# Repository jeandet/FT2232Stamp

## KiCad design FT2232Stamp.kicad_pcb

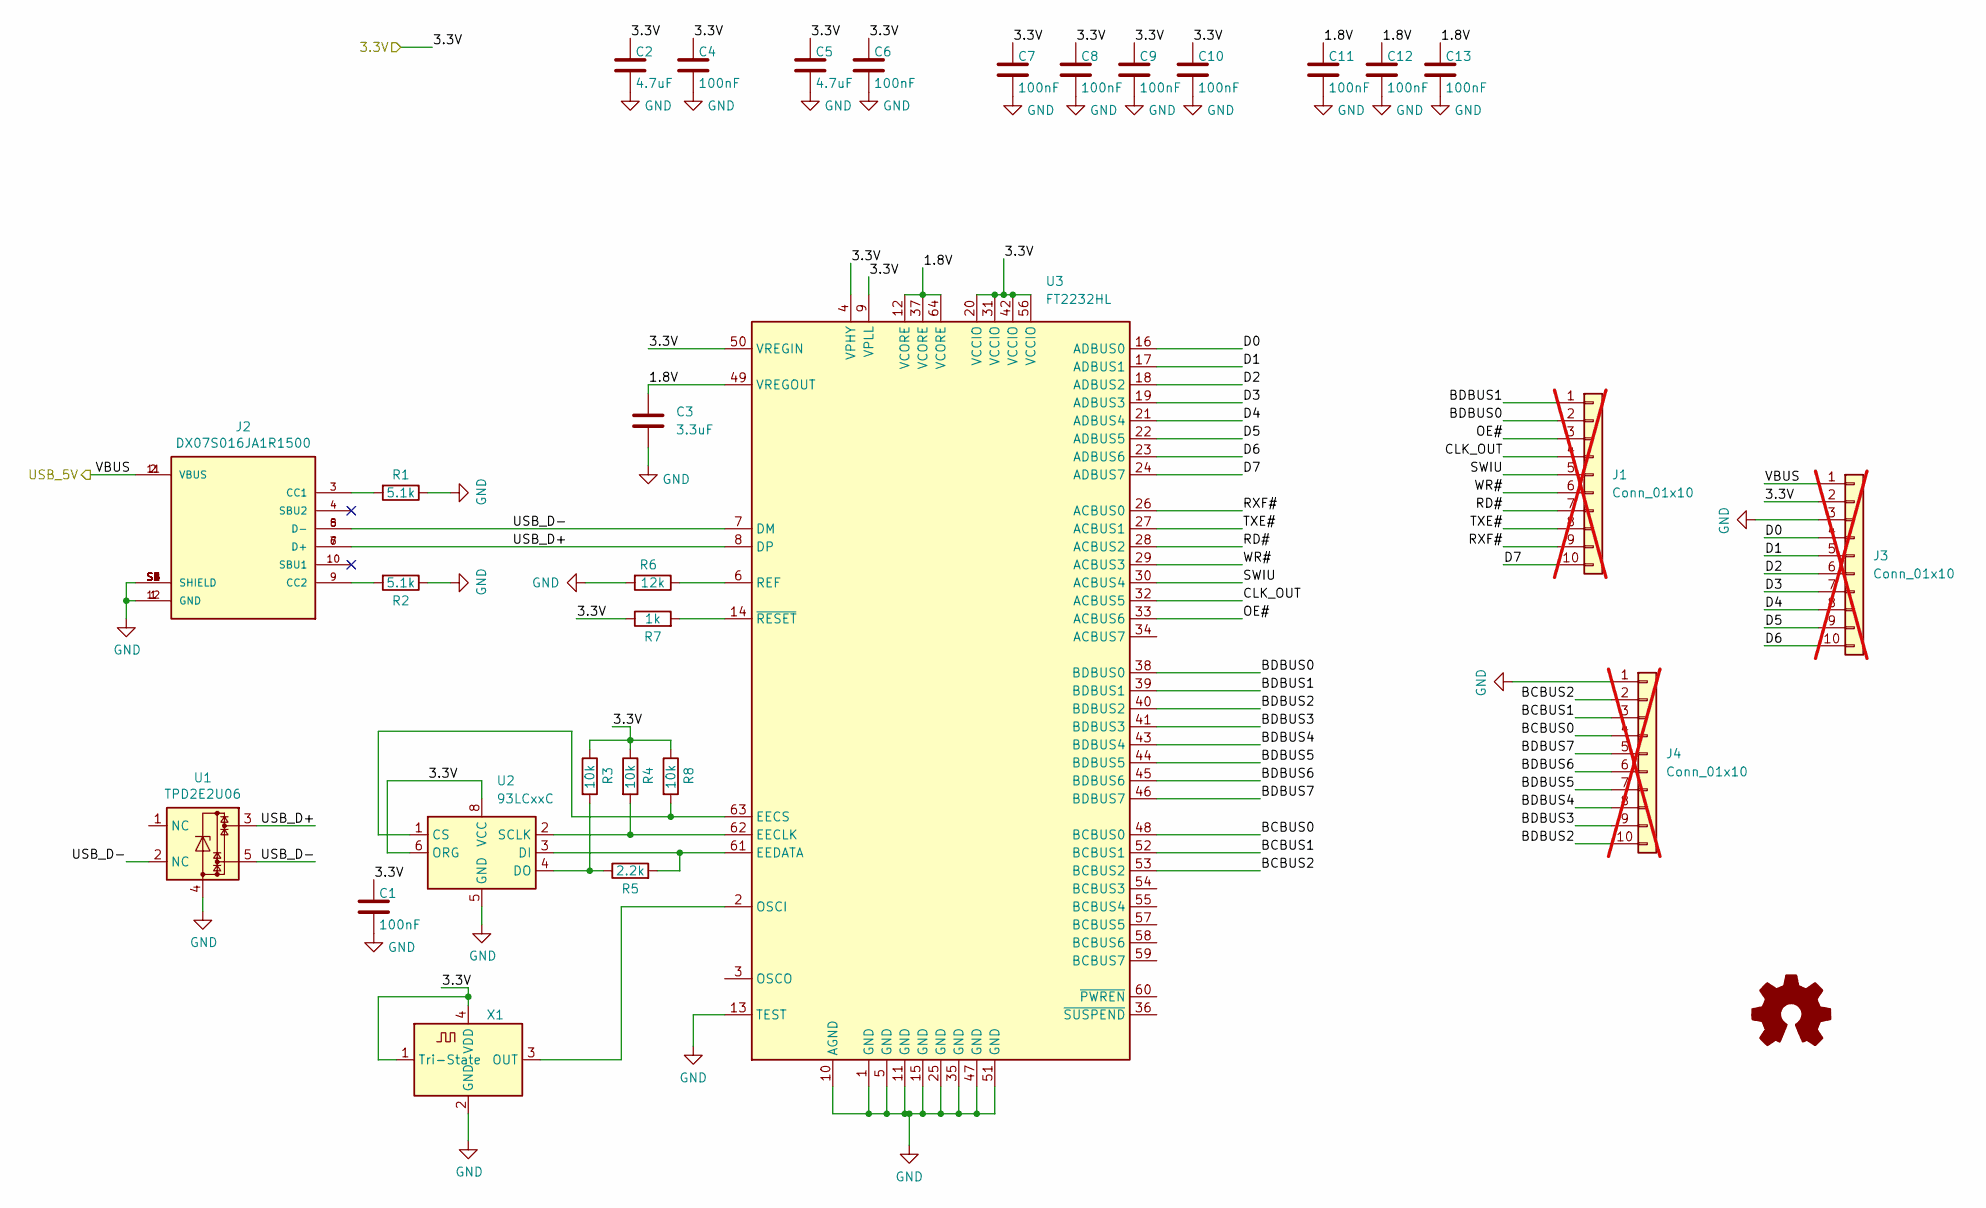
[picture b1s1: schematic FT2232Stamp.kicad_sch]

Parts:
C1, C4, C6, C7, C8, C9, C10, C11, C12, C13: 100nF; C_0402_1005Metric_Pad0.74x0.62mm_HandSolder
C2, C5: 4.7uF; C_0805_2012Metric_Pad1.18x1.45mm_HandSolder
C3: 3.3uF; C_0805_2012Metric_Pad1.18x1.45mm_HandSolder
J1, J3, J4: Conn_01x10; PinHeader_1x10_P2.54mm_Vertical; not fitted
J2: DX07S016JA1R1500; JAE_DX07S016JA1R1500; PARTREV 1
Logo1: Logo_Open_Hardware_Small; KiCad-Logo2_5mm_SilkScreen
R1, R2: 5.1k; R_0402_1005Metric
R3, R4, R8: 10k; R_0402_1005Metric_Pad0.72x0.64mm_HandSolder
R5: 2.2k; R_0402_1005Metric_Pad0.72x0.64mm_HandSolder
R6: 12k; R_0402_1005Metric_Pad0.72x0.64mm_HandSolder
R7: 1k; R_0402_1005Metric_Pad0.72x0.64mm_HandSolder
U1: TPD2E2U06; SOT-553
U2: 93LCxxC; SOIC-8_3.9x4.9mm_P1.27mm
U3: FT2232HL; LQFP-64_10x10mm_P0.5mm
X1: ECS-2520MV-xxx-xx; Oscillator_SMD_ECS_2520MV-xxx-xx-4Pin_2.5x2.0mm

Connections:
/1.8V: C3.1, C11.1, C12.1, C13.1, U3.12 (VCORE), U3.37 (VCORE), U3.49 (VREGOUT), U3.64 (VCORE)
/3.3V: C1.1, C2.1, C4.1, C5.1, C6.1, C7.1, C8.1, C9.1, C10.1, J3.2, R3.1, R4.1, R7.1, R8.1, U2.6 (ORG), U2.8 (VCC), U3.4 (VPHY), U3.9 (VPLL), U3.20 (VCCIO), U3.31 (VCCIO), U3.42 (VCCIO), U3.50 (VREGIN), U3.56 (VCCIO), X1.1 (Tri-State), X1.4 (VDD)
/BCBUS0: J4.4, U3.48 (BCBUS0)
/BCBUS1: J4.3, U3.52 (BCBUS1)
/BCBUS2: J4.2, U3.53 (BCBUS2)
/BDBUS0: J1.2, U3.38 (BDBUS0)
/BDBUS1: J1.1, U3.39 (BDBUS1)
/BDBUS2: J4.10, U3.40 (BDBUS2)
/BDBUS3: J4.9, U3.41 (BDBUS3)
/BDBUS4: J4.8, U3.43 (BDBUS4)
/BDBUS5: J4.7, U3.44 (BDBUS5)
/BDBUS6: J4.6, U3.45 (BDBUS6)
/BDBUS7: J4.5, U3.46 (BDBUS7)
/CLK_OUT: J1.4, U3.32 (ACBUS5)
/D0: J3.4, U3.16 (ADBUS0)
/D1: J3.5, U3.17 (ADBUS1)
/D2: J3.6, U3.18 (ADBUS2)
/D3: J3.7, U3.19 (ADBUS3)
/D4: J3.8, U3.21 (ADBUS4)
/D5: J3.9, U3.22 (ADBUS5)
/D6: J3.10, U3.23 (ADBUS6)
/D7: J1.10, U3.24 (ADBUS7)
/OE#: J1.3, U3.33 (ACBUS6)
/RD#: J1.7, U3.28 (ACBUS2)
/RXF#: J1.9, U3.26 (ACBUS0)
/SWIU: J1.5, U3.30 (ACBUS4)
/TXE#: J1.8, U3.27 (ACBUS1)
/USB_D+: J2.6 (D+), J2.7 (D+), U1.3, U3.8 (DP)
/USB_D-: J2.5 (D-), J2.8 (D-), U1.2 (NC), U1.5, U3.7 (DM)
/VBUS: J2.2 (VBUS), J2.11 (VBUS), J3.1
/WR#: J1.6, U3.29 (ACBUS3)
GND: C1.2, C2.2, C3.2, C4.2, C5.2, C6.2, C7.2, C8.2, C9.2, C10.2, C11.2, C12.2, C13.2, J2.1 (GND), J2.12 (GND), J2.S1 (SHIELD), J2.S2 (SHIELD), J2.S3 (SHIELD), J2.S4 (SHIELD), J2.S5 (SHIELD), J2.S6 (SHIELD), J3.3, J4.1, R1.1, R2.1, R6.2, U1.4, U2.5 (GND), U3.1 (GND), U3.5 (GND), U3.10 (AGND), U3.11 (GND), U3.13 (TEST), U3.15 (GND), U3.25 (GND), U3.35 (GND), U3.47 (GND), U3.51 (GND), X1.2 (GND)
unnamed: J2.3 (CC1), R1.2
unnamed: J2.9 (CC2), R2.2
unnamed: R8.2, U2.1 (CS), U3.63 (EECS)
unnamed: R5.2, U2.3 (DI), U3.61 (EEDATA)
unnamed: R3.2, R5.1, U2.4 (DO)
unnamed: R4.2, U2.2 (SCLK), U3.62 (EECLK)
unnamed: U3.2 (OSCI), X1.3 (OUT)
unnamed: R6.1, U3.6 (REF)
unnamed: R7.2, U3.14 (~RESET)

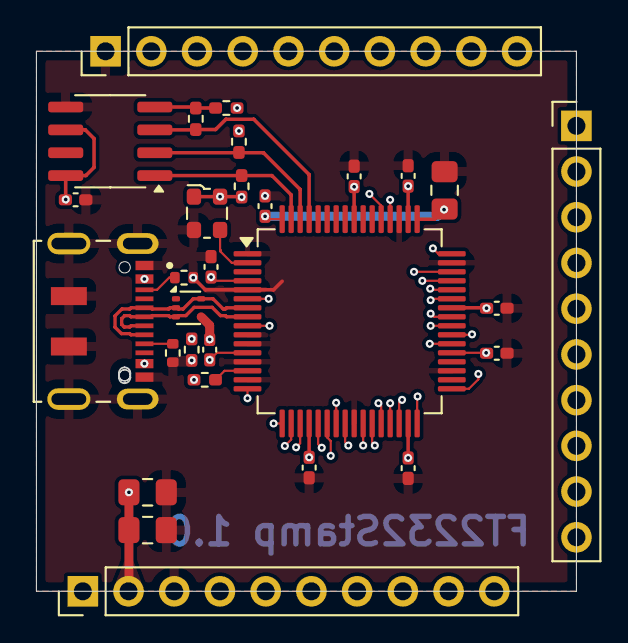
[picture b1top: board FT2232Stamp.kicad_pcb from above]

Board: 4 copper layers, 30.0 x 30.0 mm, 29 parts (0 on the bottom side), 41 nets.

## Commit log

2024-09-16 Initial release
